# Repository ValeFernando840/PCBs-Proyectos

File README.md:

# PCBs-Proyectos
Repositorio destinado a centralizar y documentar proyectos relacionados con el diseño y desarrollo de placas de circuito impreso (PCBs)

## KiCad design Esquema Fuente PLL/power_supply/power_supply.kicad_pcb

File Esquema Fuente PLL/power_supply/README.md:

## Datasheet Componentes
- VCO HMC534LP5: [Datasheet](https://www.analog.com/media/en/technical-documentation/data-sheets/hmc534.pdf)

- Sintetizador SP5769: [Datasheet](https://www.alldatasheet.com/datasheet-pdf/view/77217/MITEL/SP5769.html)

- Diodo Zener 1N4733 (5.1V): [Datasheet](https://www.alldatasheet.com/datasheet-pdf/view/58834/DIODES/1N4733A.html) 

- Diodo Zener BZX55C12 (12V): [Datasheet](https://www.vishay.com/docs/85604/bzx55.pdf)

- Tiristor TYN615 (SCR): [Datasheet](https://www.alldatasheet.es/datasheet-pdf/view/25111/STMICROELECTRONICS/TYN612.html)

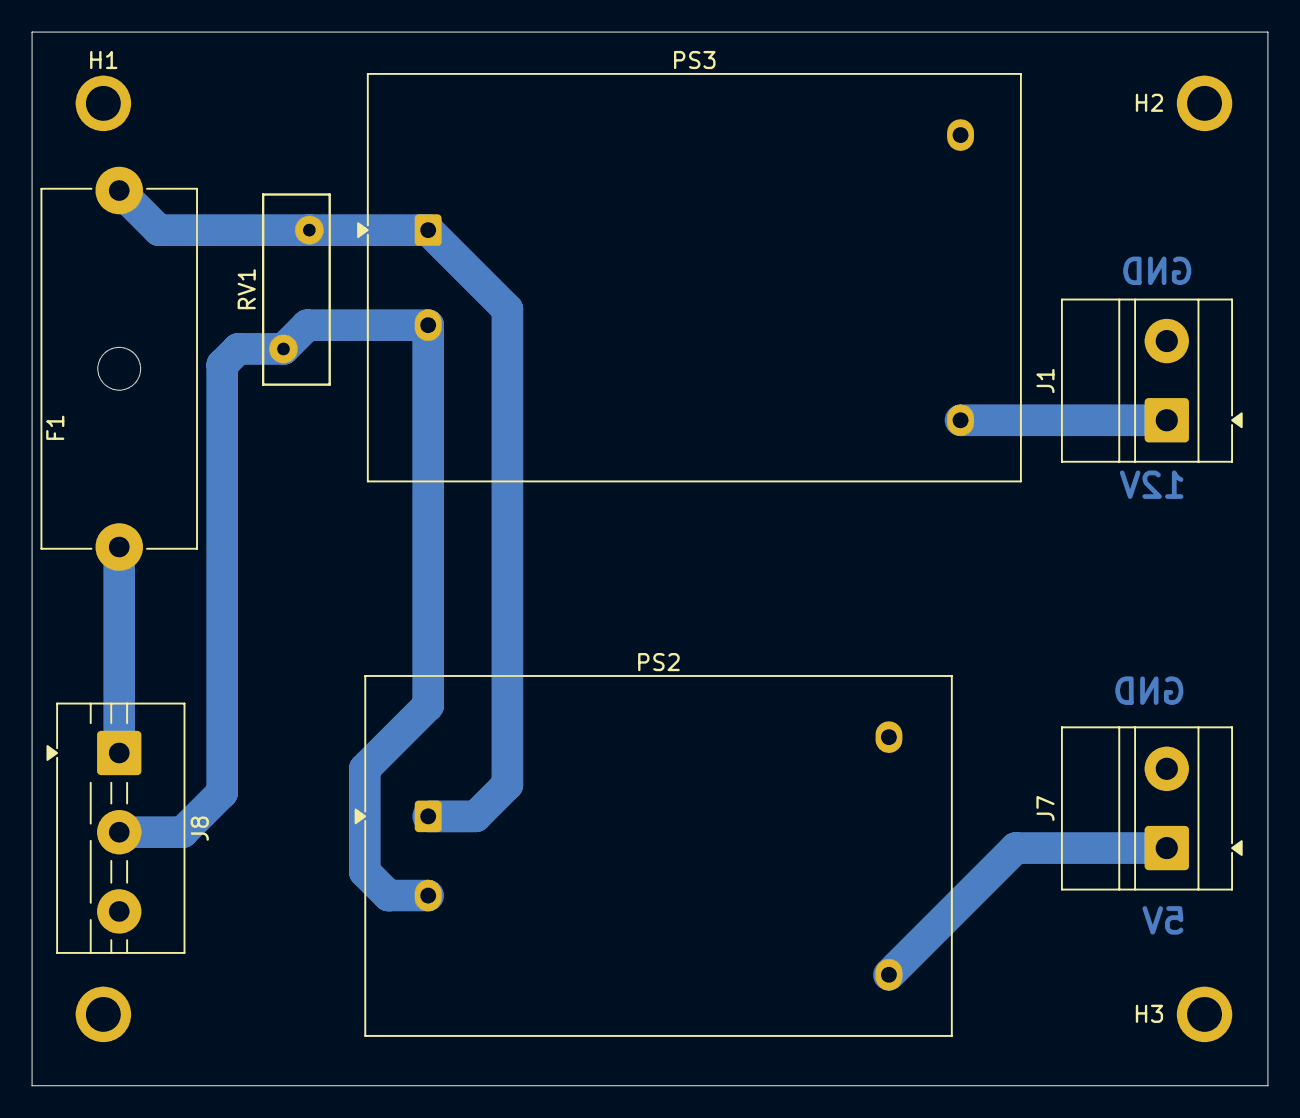
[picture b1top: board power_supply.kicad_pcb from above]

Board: 2 copper layers, 78.0 x 66.5 mm, 11 parts (1 on the bottom side), 6 nets.

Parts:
F1: Fuse; Fuseholder_Cylinder-5x20mm_Schurter_0031_8201_Horizontal_Op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
H1, H2, H3, H4: MountingHole_2.2mm_M2_ISO7380_Pad
J1, J7: Terminal_01x02; TerminalBlock_MetzConnect_Type011_RT05502HBLC_1x02_P5.00mm_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
J8: Terminal_01x03; TerminalBlock_MaiXu_MX126-5.0-03P_1x03_P5.00mm
PS2: HLK-PM01; Converter_ACDC_Hi-Link_HLK-PMxx
PS3: HLK-5M12; Converter_ACDC_Hi-Link_HLK-5Mxx
RV1: Varistor; RV_Disc_D12mm_W4.2mm_P7.5mm

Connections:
+5V: J7.1, PS2.4 (+Vout)
+12V: J1.1, PS3.4 (+Vout)
GND: J1.2, J7.2, PS2.3 (-Vout), PS3.3 (-Vout)
unnamed: F1.1, J8.1
unnamed: J8.2, PS2.2 (AC/N), PS3.2 (AC/N), RV1.2
unnamed: F1.2, PS2.1 (AC/L), PS3.1 (AC/L), RV1.1

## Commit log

2025-09-09 Se agrega carpeta Library, y primer proyecto
2025-09-10 se agrega nuevo proyecto
2025-09-12 Se agrega los links hacia los datasheet para los distintos elementos usados, se actualiza el esquemático
2025-09-16 Se agrega solo el Esquema Fuente para el sintetizador
2025-09-16 se realizaron cambios en el esquema, se agrega un varistor y se hace una div entre parte fria y caliente
2025-09-18 modificaciones en el tamaño de la pcb
2025-09-19 Se agrega pcb de crowbar
